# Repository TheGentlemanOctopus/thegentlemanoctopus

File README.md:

## Software diagram

https://github.com/TheGentlemanOctopus/thegentlemanoctopus/blob/f_octopus_code/docs/software_flow.pdf

WORK IN PROCESS FOR 2017 

Welcome to the octopus show! 

Software runs three progesses in parallel:

1. OPC Server. Either LEDSCAPE on the beaglebone or the openGL simulator at home.
2. Pattern Generator. Generates RGB data and sends to an opc server over TCP
3. RPC Client. Sends external input to the pattern generator. E.g. data from user, MSGEQ7 or .wav

## openGL Simulator ##

The openGL simulator is a fork from http://openpixelcontrol.org/ and lives in `/openpixelcontrol/`. Compiling it should be as easy as

```
$cd openpixelcontrol
$make
```

The simulator requires a json file at runtime to know where the pixels are, called a layout. For example this simple layout has a single pixel at the origin
```
[
  {
    "point": [0,0,0]
  }
]
```

### Octopus Layout ###

The module to generate an octopus is in `octopus/layouts/octopus.py`. Running this will create a default octopus.json layout that is intended to reflect the real one. 

You will notice the module contains an **Octopus** class to represent the obvious. This is further broken down into **Tentacle** and **LedStrip** classes. LedStrips contain a list of **Pixel** objects which are arranged from base to tip. Extra metadata is included in the json file so they can be imported back into Octopus objects

To make the octopus layout and start the openGL server
```
$cd octopus
$python layouts/octopus.py
$../openpixelcontrol/bin/gl_server -l layouts/octopus.json 
```

Which will run the OPC server at the usual **127.0.0.1:7890**

With the simulator up and running, we can go ahead and make some patterns!

## Pattern Generator ##

The `patternGenerator.py` module provides a command-line interface for trying out patterns and playing around with parameters. Running the module will connect to an OPC Server, display the default set of patterns and run the first pattern in the set. The **(w/s)** keys switch between patterns. You can adjust the parameters for the currently selected pattern with **(r/f), (t/g)**, etc.... It will also start an RPC Server which by default listens at **http://localhost:8000**

To run the pattern generator we need to provide an octopus

```python patternGenerator.py layouts/octopus.json```

### Making Patterns ###

Patterns are stored as classes in individual files in the `/octopus/patterns/` package. `pattern.py` contains the **Pattern** base class which all patterns inherit from. 

This contains the `register_param` method used to initialise the parameters that you tinker with in the pattern generator. This should be called in a subclass constructor before it is ever referenced. You can then get and set it just like you would any other class variable, except the values are rounded to its min/max if you try and set it beyond its limits. The module's script has a simple example.

Each implementation of Pattern should define the method `next_frame(self, octopus, data)`. When a pattern is selected, this method is called repeatedly until the pattern is switched. octopus is an instance of the Octopus in `Octopus.py` and data is a dictionary of data received by a RPC Client. The method should not return anything, but instead update the pixel colors on the Octopus object. PatternGenerator contains a default dictionary so patterns don't crash on the first iteration :/ Current defaults exist for level (volume) and a 7 band EQ 

To make a pattern you should:

1. Make a new .py file in `/octopus/patterns/` containing a class that inherits from Pattern
2. In its constructor, define parameters with `register_param` calls
3. Define a `next_frame` method that updates pixels on the octopus object
4. Import the pattern into `patternGenerator.py` module and append an instance of your new pattern to the default set in the script at the bottom
5. Run, watch and marvel :)

## RPC Client ##

An RPC Client sends data to the PatternGenerator and are stored in the `/octopus/rpcClients/` package. When the PatternGenerator receives data from a client, it updates the dictionary of data passed to `next_frame`. Clients should inherit from **RpcClient** base class, which contains the default endpoint **http://localhost:8000** and the `put` method; which should be called when sending data.

For example, `userInputClient.py` repeatedly sends key value pairs from the command line. Try selecting rpcTestPattern from the PatternGenerator and use the client to adjust the brightness with the key `level` using a value between 0-255

`streamWavClient.py` plays a .wav file while streaming level and eq data. With the PatternGenerator running try

`python rpcClients/streamWavClient.py ../examples/FFT/DaftPunk.wav`

### Running on Odroid ###

ssh to odroid
```bash
ssh odroid@192.168.1.42
```

run screen 
```bash
screen
```

run start script
```bash
./runOctopus.sh
```

to detatch screen session
```bash
ctrl+a   then d
```

to return to active session 
```bash
screen -r
```

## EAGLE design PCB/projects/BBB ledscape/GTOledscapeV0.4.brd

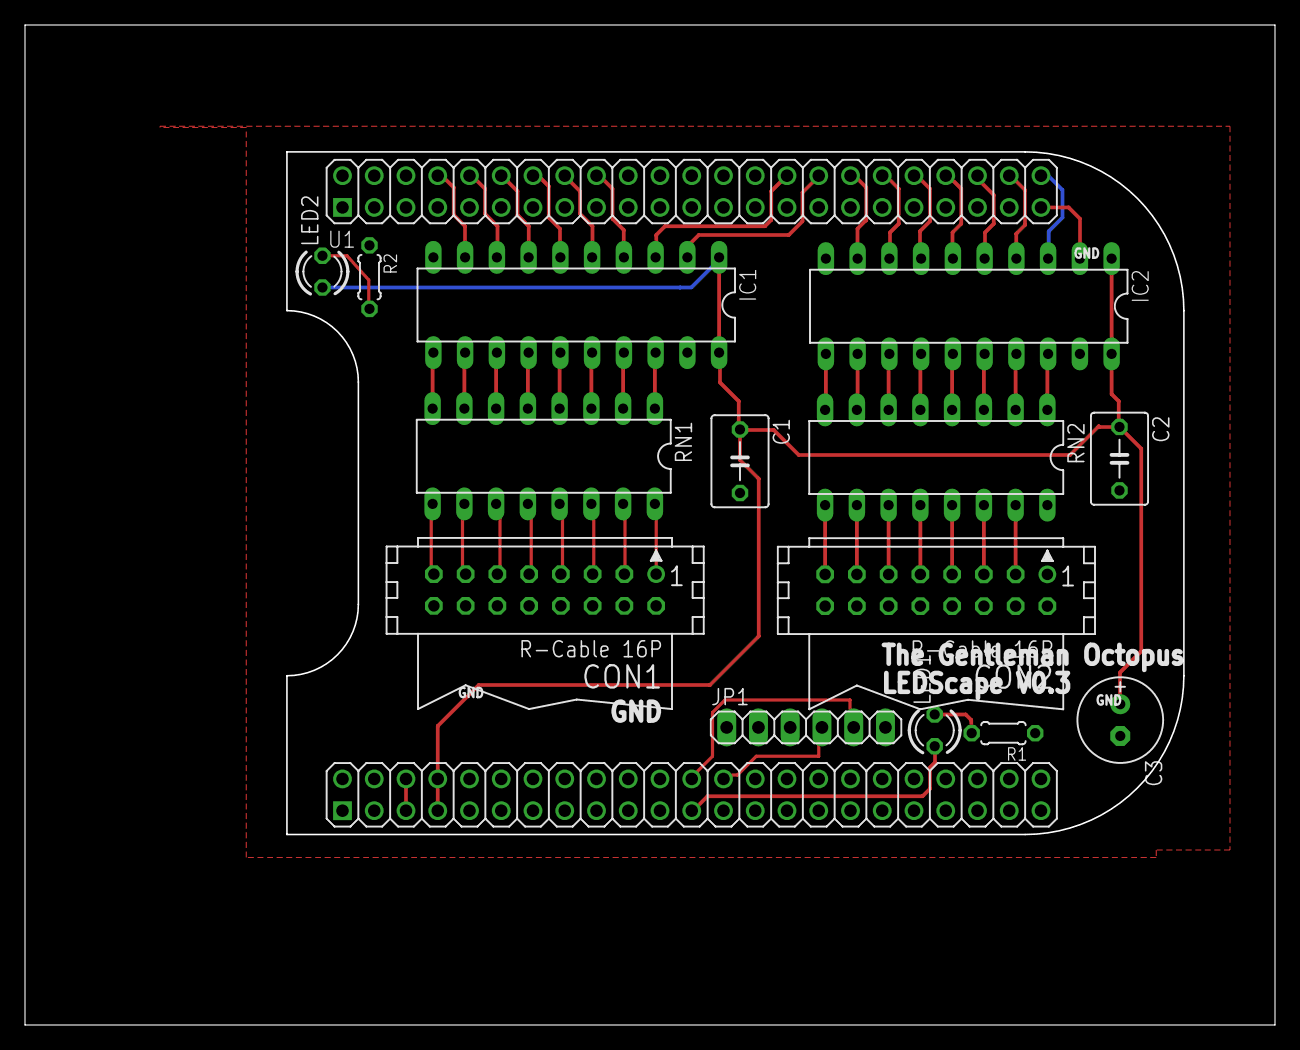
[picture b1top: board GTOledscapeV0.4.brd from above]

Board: 2 copper layers, 100.0 x 80.0 mm, 15 parts (0 on the bottom side), 56 nets.

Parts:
C1, C2: C050-045X075
C3: E2,5-7
CON1, CON2: CON16
IC1, IC2: 74HC245N; DIL20
JP1: 1X06
LED1, LED2: LED3MM
R1, R2: 0204/5
RN1, RN2: DIL16
U1: BEAGLEBONE_OUTLINE; BEAGLEBONE_SHIELD

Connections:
+5V: C1.1, C2.1, C3.+, IC1.1, IC1.20, IC2.1, IC2.20, LED2.A, U1.53, U1.54
CH00: IC1.2, U1.32
CH00_OP: CON1.1, RN1.16
CH01: IC1.3, U1.30
CH01_OP: CON1.3, RN1.15
CH02: IC1.4, U1.18
CH02_OP: CON1.5, RN1.14
CH03: IC1.5, U1.16
CH03_OP: CON1.7, RN1.13
CH04: IC1.6, U1.14
CH04_OP: CON1.9, RN1.12
CH05: IC1.7, U1.12
CH05_OP: CON1.11, RN1.11
CH06: IC1.8, U1.10
CH06_OP: CON1.13, RN1.10
CH07: IC1.9, U1.8
CH07_OP: CON1.15, RN1.9
CH08: IC2.2, U1.45
CH08_OP: CON2.1, RN2.16
CH09: IC2.3, U1.46
CH09_OP: CON2.3, RN2.15
CH10: IC2.4, U1.44
CH10_OP: CON2.5, RN2.14
CH11: IC2.5, U1.42
CH11_OP: CON2.7, RN2.13
CH12: IC2.6, U1.40
CH12_OP: CON2.9, RN2.12
CH13: IC2.7, U1.38
CH13_OP: CON2.11, RN2.11
CH14: IC2.8, U1.36
CH14_OP: CON2.13, RN2.10
CH15: IC2.9, U1.34
CH15_OP: CON2.15, RN2.9
GND: C1.2, C2.2, C3.-, CON1.2, CON1.4, CON1.6, CON1.8, CON1.10, CON1.12, CON1.14, CON1.16, CON2.2, CON2.4, CON2.6, CON2.8, CON2.10, CON2.12, CON2.14, CON2.16, IC1.10, IC1.19, IC2.10, IC2.19, JP1.1, R1.1, R2.1, U1.1, U1.2, U1.47, U1.48, U1.89, U1.90, U1.91, U1.92
unnamed: IC2.18, RN2.1
unnamed: LED2.K, R2.2
unnamed: LED1.K, R1.2
unnamed: LED1.A, U1.69
unnamed: IC2.17, RN2.2
unnamed: IC1.18, RN1.1
unnamed: IC1.17, RN1.2
unnamed: IC1.16, RN1.3
unnamed: IC1.15, RN1.4
unnamed: IC1.14, RN1.5
unnamed: IC1.13, RN1.6
unnamed: IC2.16, RN2.3
unnamed: IC2.15, RN2.4
unnamed: IC2.14, RN2.5
unnamed: IC2.13, RN2.6
unnamed: IC2.12, RN2.7
unnamed: IC2.11, RN2.8
unnamed: IC1.12, RN1.7
unnamed: IC1.11, RN1.8
UART1_RXD: JP1.4, U1.72
UART1_TXD: JP1.5, U1.70
VDD_5V: U1.51, U1.52

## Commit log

2017-04-15 Set theme jekyll-theme-midnight
2017-04-27 PCB designs added
2017-06-09 last of PCB files added
2017-06-09 dumping old cold to tidy up
2017-06-14 PCB updated to use the 74AHCT245 chip instead of the other level shifter. Should work better for going from 3v3 to 5v
2017-06-17 shifter chip spec sheet added
2017-06-17 adding dummy unit tests
2017-06-17 Finished PCB and Ting
2017-06-17 mocking opc server
2017-06-18 added timeout
2017-06-18 global .gitignore
2017-06-24 need for speed?
2017-06-30 opc.py & color_utils.py missing from repo. Now added.
2017-06-30 gerber files added. These have been sent to PCB way for the new PCB
2017-07-01 measuring framerate for test
2017-07-01 getting rid of strict option
2017-07-01 making pg more speed testable, mocks aren't consistent in their timing
2017-07-01 test function for speed test
2017-07-22 nicer thing
2017-07-22 logging framerates to file
2017-07-23 logging test data into csv
2017-07-23 mock opc server (empty tcp server), this will probably deprecate
2017-07-23 speed test data class
2017-07-23 adding argparse for speed tests
2017-07-23 plotting speed tests
2017-07-23 printing results
2017-07-23 more pwintang
2017-07-23 nicer plotting
2017-07-23 ignoring .csv in source
2017-07-23 fun with *args
2017-07-23 restoring pg unit tests
2017-07-23 patternStreamData
2017-07-23 plugging PatternStreamData into pg
2017-07-23 siney time for the unstimulated octopus
2017-07-23 naming conventions
2017-07-23 moving opc dispatch back into update
2017-07-23 keeping it classy, sd
2017-07-23 integration test called is
2017-07-23 non blocking cpu meter
2017-07-23 because ima in a unit testin kinda mood
2017-07-23 making patterns using new stream data object
2017-07-23 fixing unit tests
2017-07-23 prepping for status
2017-07-23 displying current pattern in pattern generator tests
2017-07-25 boot script for odroid added
2017-07-25 removing utils
2017-07-25 removing deprecated refdems
2017-07-25 adding back imports
2017-07-25 ip and port for integration test
2017-07-27 keyboard client to xmlrpc server added
2017-07-28 scene code added
2017-07-28 Software diagre and comprehensive config file added
2017-07-28 Update README.md
    readme brought over from bitbucket, will need updating
2017-07-28 made diagram pretty
2017-07-29 renaming pattern generator to gentleman octopus
2017-07-29 better naming for octopus layout
2017-07-29 spiralTown
2017-07-29 adding audio stream queue to TGO
2017-07-29 moving run to device class
2017-07-29 this change implies I should be developing something more useful..
2017-07-29 fixing ocotpus main
2017-07-29 time ting
2017-07-30 filename for integration tests
2017-07-30 printing full stack trace on pattern exception:
2017-07-30 updating eq pattern for tentacles
2017-07-30 sample period when loading integration test csv
2017-07-30 default pattern list:
2017-07-30 co-ments
2017-07-30 AudioProcessing moule created
2017-07-30 AudioProcessing test __main__ added
2017-07-30 lavalamp 2
2017-07-30 Udpserver fixes, comments and remove elwire stuff
2017-07-30 AudioProcessing simulated data added from config file
2017-07-30 clean up for merge
2017-07-30 laval lamp not slow
2017-07-30 passing config args through to udp server
2017-07-30 spiral out still get choppy
2017-07-30 arg parsing for csv writer
2017-07-30 added the csv files
2017-07-30 scene updated with changes to make new fish and octopus as devices
2017-07-30 Turned off the autoscaling by default.
2017-07-30 spiral out doesnt slow down
2017-07-30 stream csv file
2017-07-30 sending over udp
2017-07-30 framein the rate
2017-07-30 patching up udp server to integration test
2017-07-30 GTO eq data should be tuple
2017-07-31 port settings for udp csv stream
2017-07-31 plotting a csv of fft
2017-07-31 loading csv during integration tests
2017-07-31 comments
2017-07-31 dded new pattern to play with, changed csvstreamer rate to same as arduino
2017-07-31 carousel pattern and rotate
2017-07-31 more accessible default octopus
2017-07-31 scene now runs the octopus
2017-07-31 colourful
2017-07-31 spinny both directions
2017-07-31 slightly more colourful
2017-07-31 carosellin
2017-08-01 towards hsv
2017-08-01 fixing broken refs
2017-08-01 BUGFIX: GTO queue out of order
2017-08-01 the gentlemans run
2017-08-01 new config for hardware added
2017-08-01 deleting mpl ref
2017-08-01 config ip fixed
2017-08-01 pixels in separate channels
2017-08-01 undoing separate channel thing
2017-08-01 better disabling of status monitor
2017-08-01 renaming in git sucks
2017-08-01 lowercase carousel
2017-08-01 tweaking LL2 params
2017-08-02 simple rpc test client modified
2017-08-02 run_new.py copied in to run.py for cleaner repo logic
2017-08-02 time out now passes through from run
2017-08-02 carousel2
2017-08-02 angular velocity
2017-08-02 Update README.md
    instructions to run screen for uninterrupted performance when ssh session closed.
2017-08-02 ignoring subl project files
2017-08-02 swirlly
2017-08-02 playing around with defua.ts
2017-08-02 hue offset
2017-08-02 cleaning up names
2017-08-02 more efficeint carousel
2017-08-02 adding carousel to shambala
2017-08-02 boot now refers to run.py
2017-08-02 ignoring sublime projects
2017-08-02 mantle object
2017-08-02 mantely
2017-08-02 TGO outputs mantle pixels
2017-08-02 hue jams
2017-08-02 EL wire enabled
2017-08-02 config stuff
2017-08-02 beat channel for EqPattern
2017-08-02 temp change will remove print
2017-08-02 stuff
2017-08-02 enable GO status monitor in config
2017-08-02 fish didnt refer to self in serial queue
2017-08-02 fish had no while loop! fixing!
2017-08-02 set brightness in config
2017-08-02 fish queues corrected?
2017-08-02 more effecient contracting
2017-08-02 conf chages
2017-08-02 disabling carouse; :(
2017-08-03 max switch rate on eq pattern
2017-08-14 BUGFIX: hue mod
2017-08-15 BUGFIX: carousel hue offset not progressing
2017-08-15 bugfix: safer queue taking in tgo
2017-08-15 changed ip for arduino
2017-09-19 Eclipse IDE environment set up for the ESP32 framework.
2017-09-20 Started work on the project. Reorganised the directory a bit. Fixed some include issues. I think it's good to go!
2017-10-03 Start work on the pixel structs to run the neopixel channel drivers
2017-10-13 Update README.md
    typo
2017-10-21 End of day. Structs and stuff started. Getting going.
2017-10-23 Setup of LED structures and the like.
2017-10-24 RMT working!
2017-10-26 Implemented crude neopixel sending from RMT. Whack into a function
2017-10-30 RBG to pixel works for a single buffer! strange behaviour where it skips first pixel for some reason... Need to fill buffer on interrupt next. Make faster.
2017-10-31 A bit more stable
2017-10-31 Started putting driver into its own function that can be called from the interrupt. Work on the continuously sending data. Bug where if RMT blockis full it doesn't continously send...
2017-11-07 Pixel wraparound enabled. Now getting ready to start the interrupt functions.
2017-11-09 Fix for if RMT breaks loop half way through pixel. Beginning of rtos calls
2017-11-17 Looping RMT buffer now works. Should decide how to implement on limited cores but will probably stay how it is.
2017-11-17 PIXEL DRIVER WORKS! Needs testing fully but next stop is setting up programatically.
2017-11-19 backup new cube code
2017-11-19 better structure now defined.
2017-11-20 folder renamed from octopus_code to code. cube code now arranged to fit logical folder structure. All master files in master folder. All new devices will then have new folder like with the cube and i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
2017-11-20 stray file deleted
2017-11-20 New animation subclass Cube_animation created to be the master animation file for cube specific animations
2017-11-20 deleted stray files
2017-11-20 Commented the pixel interface. Just need to write the channel generator now and it's done. Copied across the arduino rainbow code to show off. Tested upto 5000 leds!
2017-11-22 Added a function to generate the pixel structures from given parameters. Tried doing 8 pixel channels at once but it got a bit unhappy....
2017-11-25 Experimentation into making the pixel driver faster. Limit seems to be 6 comfortably. Also limited the pixel driver to core1
2017-11-29 Rearranged some of the stuff in the pixel driver to try and make it better. Switched to a shared interrupt handler for the RMT interrupts also.
2017-12-07 more animations added and random change every 10 seconds
2017-12-07 now drives multiple independant devices
2017-12-08 Pretty huge update. Pixel driver doesn't continuously send anymore, it will only update the strip when needed. Need to do the OS calls and semaphores, but I think the majority of the framework is in 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
2017-12-09 Set the pixel driver to use both half way and end interrupts. End interrupts are used for synchronising, as the half way ones seemed to go a bit out...
2017-12-11 Switched to an rtos and semaphore based implememtation to try and get the timings right. Still not perfect but getting there..
2017-12-12 Ergh, Still chasing this sync bug down...
2017-12-14 Driver is back in a working state!, sends out patterns again now up to 8 channels in a much more stable fashion!
2017-12-29 Pixel driver finished and works. Requires a level shifter for longer LED strips.
